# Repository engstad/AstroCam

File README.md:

# AstroCam

My hobby project is to create a camera suitable for astronomy pictures. Here you can follow my work. It is slow going, since I don't have much time to allocate for this. So don't expect too many updates.

For now I have been focusing on three things:

1. understanding Analog Device's H-driver and ADC chip ADDI7013,
2. creating the power circuitry required for the many chips,
3. creating the PCB for the CCD camera chip.

So far, only V0.2 of the ADDI breakout board has been produced and I'm in the process of testing it:

And it works!

So, that means that I'll start working on the camera parts next.

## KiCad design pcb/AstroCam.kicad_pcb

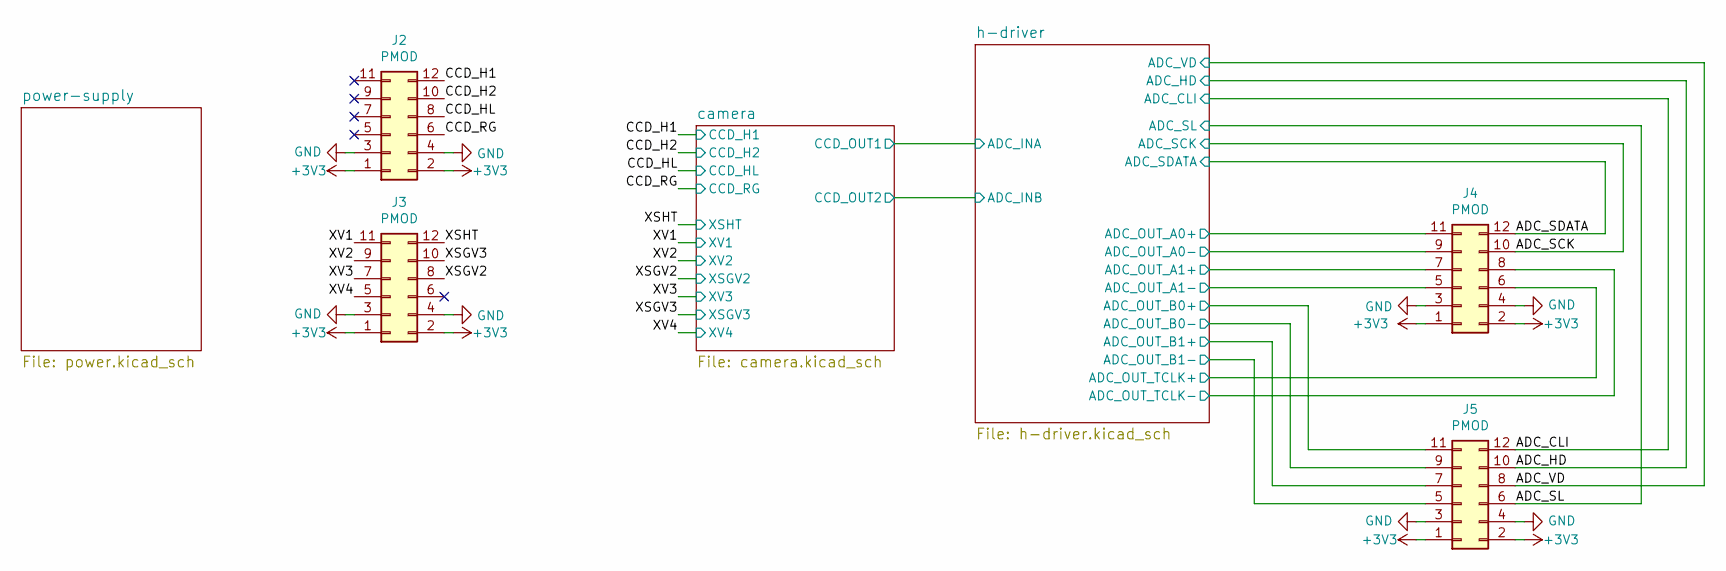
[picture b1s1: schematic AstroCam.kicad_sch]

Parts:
J2, J3, J4, J5: PMOD; PinHeader_2x06_P2.54mm_Horizontal

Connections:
+3V3: J2.1, J2.2, J3.1, J3.2, J4.1, J4.2, J5.1, J5.2; also elsewhere on the board
/ADC_CLI: J5.12; also elsewhere on the board
/ADC_HD: J5.10; also elsewhere on the board
/ADC_SCK: J4.10; also elsewhere on the board
/ADC_SDATA: J4.12; also elsewhere on the board
/ADC_SL: J5.6; also elsewhere on the board
/ADC_VD: J5.8; also elsewhere on the board
/CCD_H1: J2.12; also elsewhere on the board
/CCD_H2: J2.10; also elsewhere on the board
/CCD_HL: J2.8; also elsewhere on the board
/CCD_RG: J2.6; also elsewhere on the board
/XSGV2: J3.8; also elsewhere on the board
/XSGV3: J3.10; also elsewhere on the board
/XSHT: J3.12; also elsewhere on the board
/XV1: J3.11; also elsewhere on the board
/XV2: J3.9; also elsewhere on the board
/XV3: J3.7; also elsewhere on the board
/XV4: J3.5; also elsewhere on the board
/h-driver/ADC_OUT_A0+: J4.11; also elsewhere on the board
/h-driver/ADC_OUT_A0-: J4.9; also elsewhere on the board
/h-driver/ADC_OUT_A1+: J4.7; also elsewhere on the board
/h-driver/ADC_OUT_A1-: J4.5; also elsewhere on the board
/h-driver/ADC_OUT_B0+: J5.11; also elsewhere on the board
/h-driver/ADC_OUT_B0-: J5.9; also elsewhere on the board
/h-driver/ADC_OUT_B1+: J5.7; also elsewhere on the board
/h-driver/ADC_OUT_B1-: J5.5; also elsewhere on the board
/h-driver/ADC_OUT_TCLK+: J4.6; also elsewhere on the board
/h-driver/ADC_OUT_TCLK-: J4.8; also elsewhere on the board

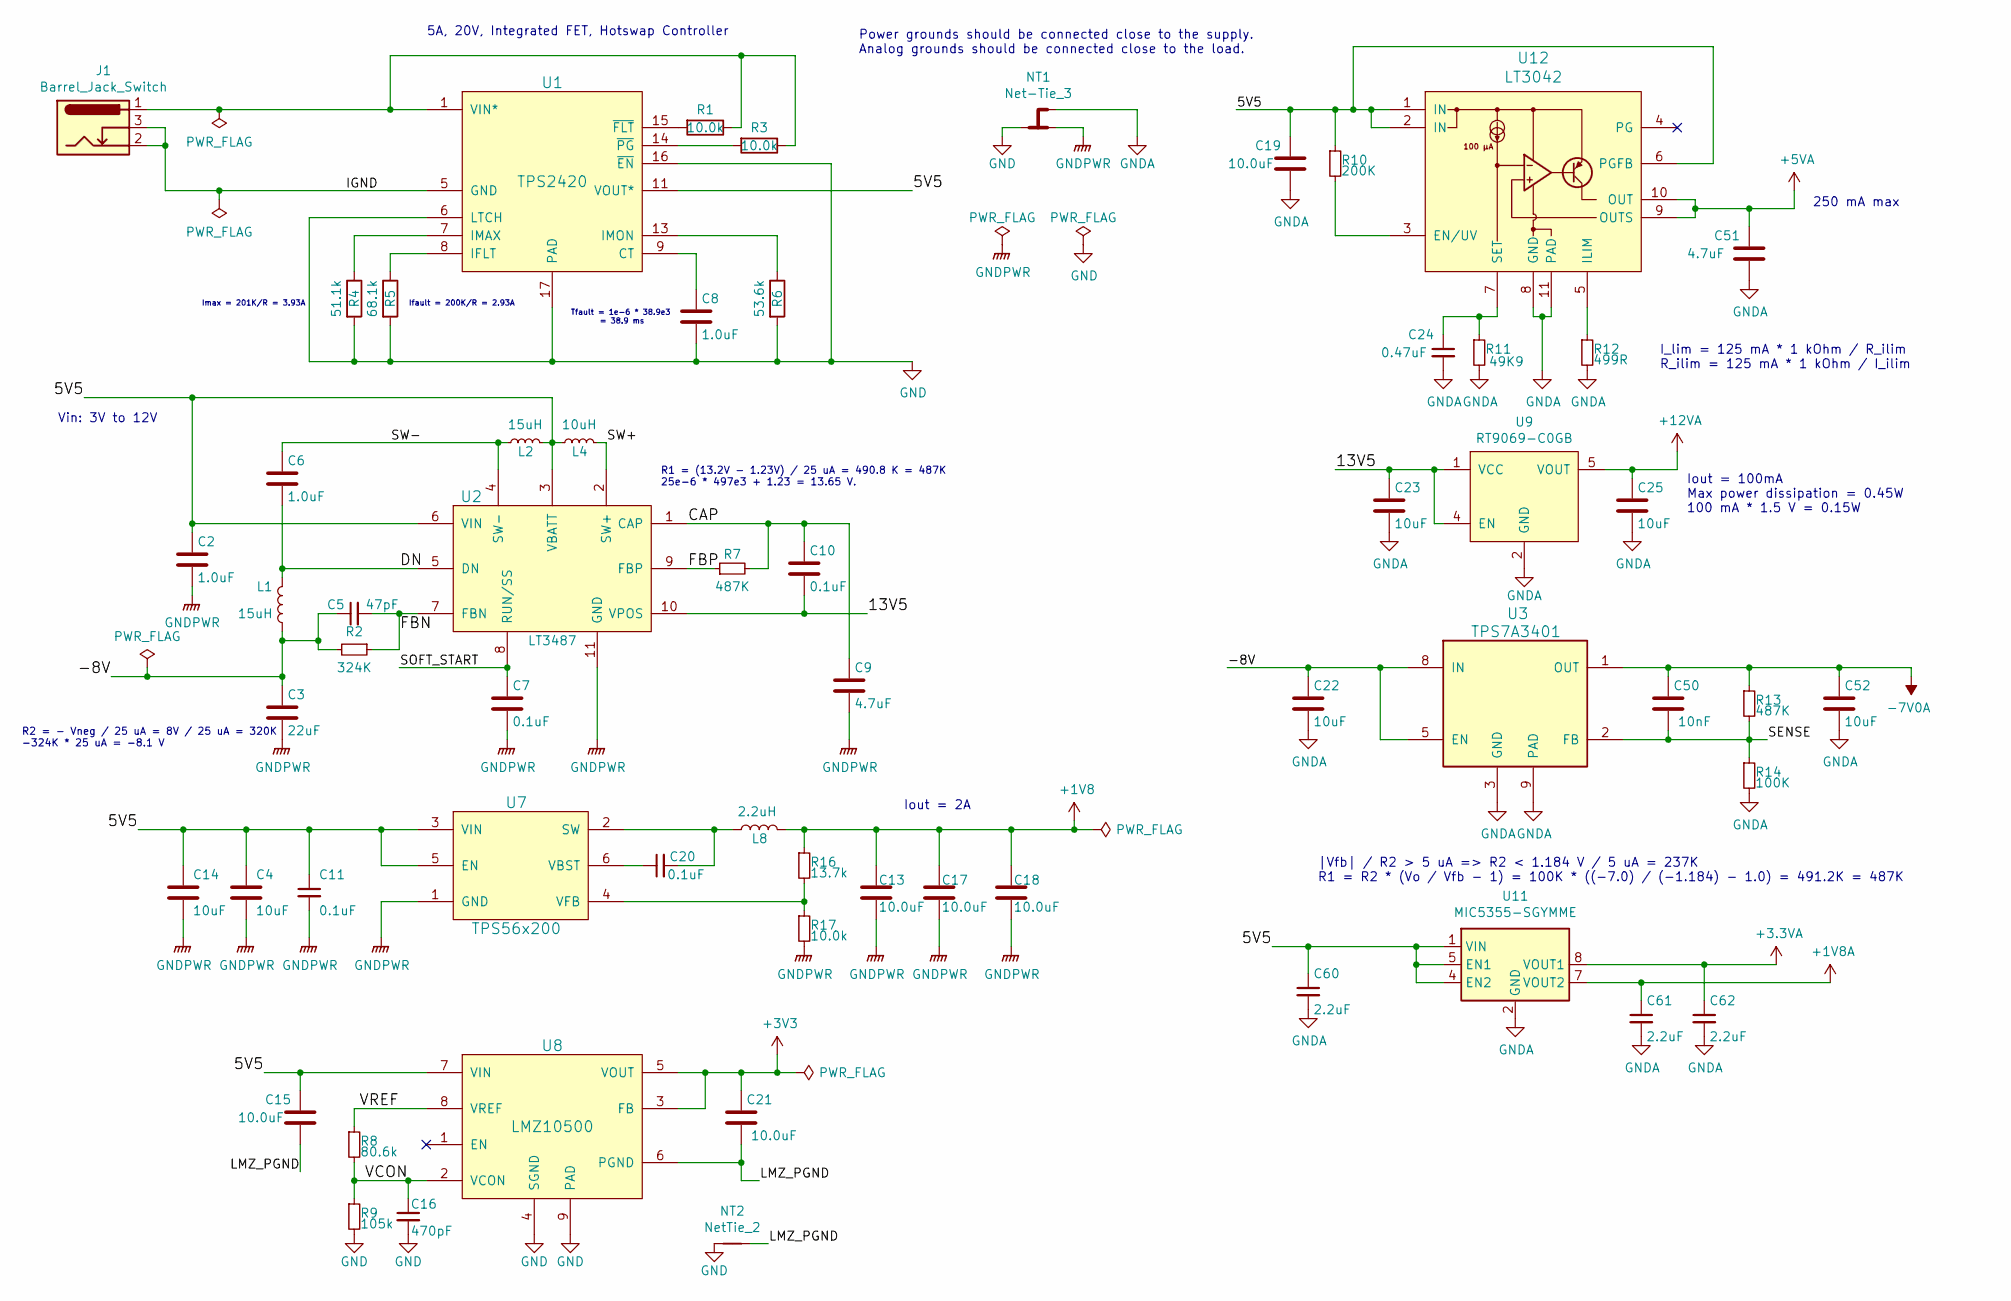
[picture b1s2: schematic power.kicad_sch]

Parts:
C2, C6, C8: 1.0uF; C_0603_1608Metric
C3: 22uF; C_1206_3216Metric
C4, C14: 10uF; C_0805_2012Metric
C5: 47pF; C_0603_1608Metric
C7, C10, C11, C20: 0.1uF; C_0603_1608Metric
C9, C51: 4.7uF; C_0805_2012Metric
C13, C17, C18, C19: 10.0uF; C_1206_3216Metric
C15, C21: 10.0uF; C_0805_2012Metric
C16: 470pF; C_0603_1608Metric
C22, C23, C25, C52: 10uF; C_1206_3216Metric
C24: 0.47uF; C_0603_1608Metric
C50: 10nF; C_0603_1608Metric
C60, C61, C62: 2.2uF; C_0603_1608Metric
J1: Barrel_Jack_Switch; BarrelJack_Wuerth_6941xx301002
L1, L2: 15uH; L_Wurth-4018
L4: 10uH; L_Wurth-4018
L8: 2.2uH; L_0805_2012Metric
NT1: Net-Tie_3; NetTie-3_SMD_Pad0.5mm
NT2: NetTie_2; NetTie-2_THT_Pad0.3mm
R1, R3, R17: 10.0k; R_0603_1608Metric
R2: 324K; R_0603_1608Metric
R4: 51.1k; R_0603_1608Metric
R5: 68.1k; R_0603_1608Metric
R6: 53.6k; R_0603_1608Metric
R7, R13: 487K; R_0603_1608Metric
R8: 80.6k; R_0603_1608Metric
R9: 105k; R_0603_1608Metric
R10: 200K; R_0603_1608Metric
R11: 49K9; R_0603_1608Metric
R12: 499R; R_0603_1608Metric
R14: 100K; R_0603_1608Metric
R16: 13.7k; R_0603_1608Metric
U1: TPS2420; QFN-16-1EP_4x4mm_P0.65mm_EP2.7x2.7mm_ThermalVias
U2: LT3487; DFN-10-1EP_3x3mm_P0.5mm_EP1.7x2.5mm
U3: TPS7A3401; VSSOP-8_3.0x3.0mm_P0.65mm
U7: TPS56x200; SOT-23-6
U8: LMZ10500; Texas_Instruments-LLP-8
U9: RT9069-C0GB; SOT-23-5
U11: MIC5355-SGYMME; MSOP-8-1EP_3x3mm_P0.65mm_EP2.5x3mm_Mask1.73x2.36mm_ThermalV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
U12: LT3042; DFN-10-1EP_3x3mm_P0.5mm_EP1.65x2.38mm_ThermalVias

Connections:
+1V8: C13.1, C17.1, C18.1, L8.2, R16.1; also elsewhere on the board
+1V8A: C61.1, U11.7 (VOUT2)
+3.3VA: C62.1, U11.8 (VOUT1); also elsewhere on the board
+3V3: C21.1, U8.3 (FB), U8.5 (VOUT); also elsewhere on the board
+5VA: C51.1, U12.9 (OUTS), U12.10 (OUT); also elsewhere on the board
+12VA: C25.1, U9.5 (VOUT); also elsewhere on the board
-7V0A: C50.1, C52.1, R13.1, U3.1 (OUT); also elsewhere on the board
/power-supply/5V5: C2.1, C4.1, C11.1, C14.1, C15.1, C19.1, C60.1, L2.2, L4.1, R10.1, U1.10 (VOUT*), U1.11 (VOUT*), U1.12 (VOUT*), U2.3 (VBATT), U2.6 (VIN), U7.3 (VIN), U7.5 (EN), U8.7 (VIN), U11.1 (VIN), U11.4 (EN2), U11.5 (EN1), U12.1 (IN), U12.2 (IN), U12.6 (PGFB)
/power-supply/13V5: C10.2, C23.1, U2.10 (VPOS), U9.1 (VCC), U9.4 (EN)
/power-supply/-8V: C3.1, C5.1, C22.1, L1.1, R2.2, U3.5 (EN), U3.8 (IN)
/power-supply/CAP: C9.1, C10.1, R7.2, U2.1 (CAP)
/power-supply/DN: C6.2, L1.2, U2.5 (DN)
/power-supply/FBN: C5.2, R2.1, U2.7 (FBN)
/power-supply/FBP: R7.1, U2.9 (FBP)
/power-supply/IGND: J1.2, J1.3, U1.5 (GND)
/power-supply/LMZ_PGND: C15.2, C21.2, NT2.2, U8.6 (PGND)
/power-supply/SENSE: C50.2, R13.2, R14.1, U3.2 (FB)
/power-supply/SOFT_START: C7.1, U2.8 (RUN/SS)
/power-supply/SW+: L4.2, U2.2 (SW+)
/power-supply/SW-: C6.1, L2.1, U2.4 (SW-)
/power-supply/VCON: C16.1, R8.2, R9.1, U8.2 (VCON)
/power-supply/VREF: R8.1, U8.8 (VREF)
GNDPWR: C2.2, C3.2, C4.2, C7.2, C9.2, C11.2, C13.2, C14.2, C17.2, C18.2, NT1.1, R17.2, U2.11 (GND), U7.1 (GND)
unnamed: C8.1, U1.9 (CT)
unnamed: R5.1, U1.8 (IFLT)
unnamed: R4.1, U1.7 (IMAX)
unnamed: R6.1, U1.13 (IMON)
unnamed: R1.2, U1.15 (~FLT)
unnamed: R3.2, U1.14 (~PG)
unnamed: C20.2, L8.1, U7.2 (SW)
unnamed: C20.1, U7.6 (VBST)
unnamed: R16.2, R17.1, U7.4 (VFB)
unnamed: R10.2, U12.3 (EN/UV)
unnamed: R12.1, U12.5 (ILIM)
unnamed: C24.1, R11.1, U12.7 (SET)
VIN*: J1.1, R1.1, R3.1, U1.1 (VIN*), U1.2 (VIN*), U1.3 (VIN*), U1.4 (VIN*)

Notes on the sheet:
R2 = - Vneg / 25 uA = 8V / 25 uA = 320K -324K * 25 uA = -8.1 V
Iout = 2A
I_lim = 125 mA * 1 kOhm / R_ilim R_ilim = 125 mA * 1 kOhm / I_ilim
Tfault = 1e-6 * 38.9e3 = 38.9 ms
250 mA max
Vin: 3V to 12V
Ifault = 200K/R = 2.93A
Imax = 201K/R = 3.93A
Power grounds should be connected close to the supply. Analog grounds should be connected close to the load.
R1 = (13.2V - 1.23V) / 25 uA = 490.8 K = 487K 25e-6 * 497e3 + 1.23 = 13.65 V.
|Vfb| / R2 > 5 uA => R2 < 1.184 V / 5 uA = 237K R1 = R2 * (Vo / Vfb - 1) = 100K * ((-7.0) / (-1.184) - 1.0) = 491.2K = 487K
Iout = 100mA Max power dissipation = 0.45W 100 mA * 1.5 V = 0.15W
5A, 20V, Integrated FET, Hotswap Controller

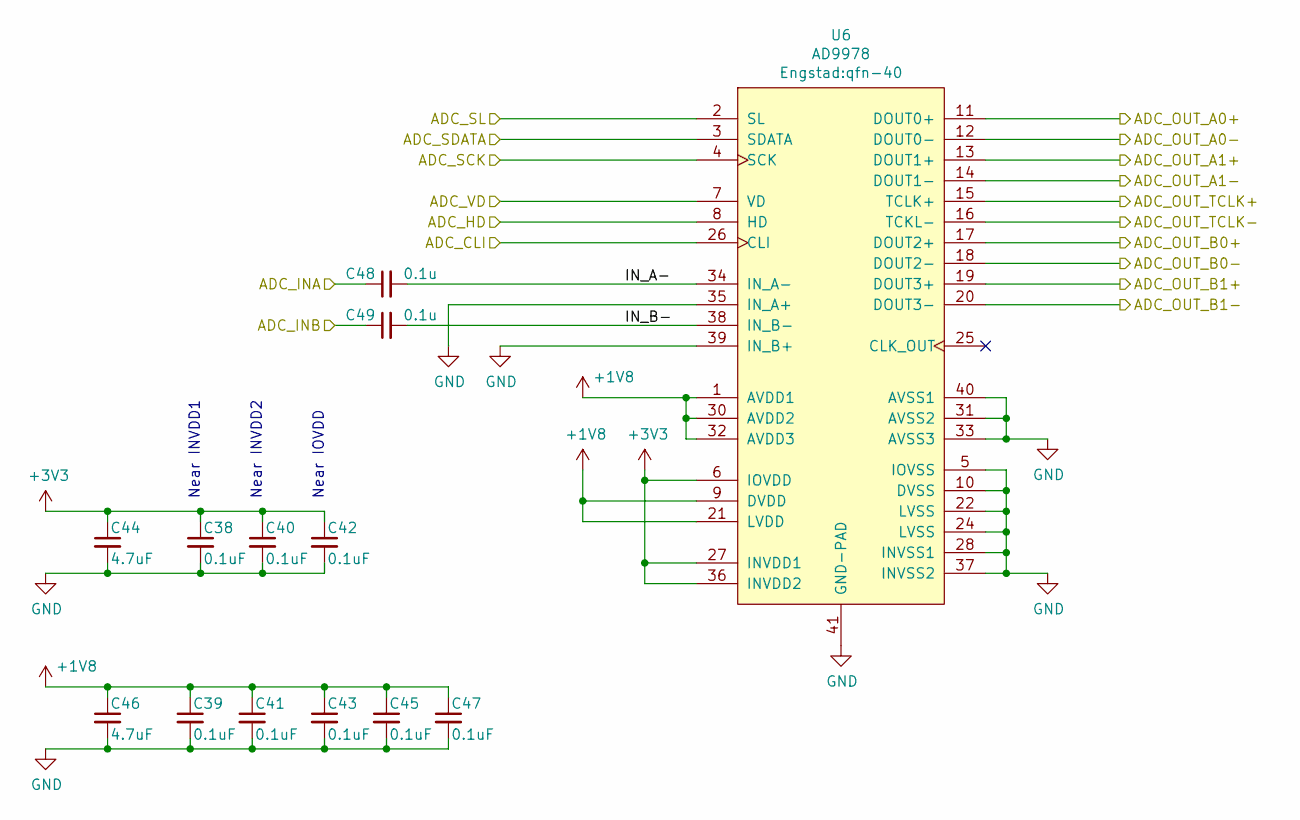
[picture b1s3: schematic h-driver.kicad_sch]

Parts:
C38, C39, C40, C41, C42, C43, C45, C47: 0.1uF; C_0603_1608Metric
C44, C46: 4.7uF; C_0805_2012Metric
C48, C49: 0.1u; C_0603_1608Metric
U6: AD9978; qfn-40

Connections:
+1V8: C39.1, C41.1, C43.1, C45.1, C46.1, C47.1, U6.1 (AVDD1), U6.9 (DVDD), U6.21 (LVDD), U6.30 (AVDD2), U6.32 (AVDD3); also elsewhere on the board
+3V3: C38.1, C40.1, C42.1, C44.1, U6.6 (IOVDD), U6.27 (INVDD1), U6.36 (INVDD2); also elsewhere on the board
/ADC_CLI: U6.26 (CLI); also elsewhere on the board
/ADC_HD: U6.8 (HD); also elsewhere on the board
/ADC_SCK: U6.4 (SCK); also elsewhere on the board
/ADC_SDATA: U6.3 (SDATA); also elsewhere on the board
/ADC_SL: U6.2 (SL); also elsewhere on the board
/ADC_VD: U6.7 (VD); also elsewhere on the board
/camera/CCD_OUT1: C48.1; also elsewhere on the board
/camera/CCD_OUT2: C49.1; also elsewhere on the board
/h-driver/ADC_OUT_A0+: U6.11 (DOUT0+); also elsewhere on the board
/h-driver/ADC_OUT_A0-: U6.12 (DOUT0-); also elsewhere on the board
/h-driver/ADC_OUT_A1+: U6.13 (DOUT1+); also elsewhere on the board
/h-driver/ADC_OUT_A1-: U6.14 (DOUT1-); also elsewhere on the board
/h-driver/ADC_OUT_B0+: U6.17 (DOUT2+); also elsewhere on the board
/h-driver/ADC_OUT_B0-: U6.18 (DOUT2-); also elsewhere on the board
/h-driver/ADC_OUT_B1+: U6.19 (DOUT3+); also elsewhere on the board
/h-driver/ADC_OUT_B1-: U6.20 (DOUT3-); also elsewhere on the board
/h-driver/ADC_OUT_TCLK+: U6.15 (TCLK+); also elsewhere on the board
/h-driver/ADC_OUT_TCLK-: U6.16 (TCKL-); also elsewhere on the board
/h-driver/IN_A-: C48.2, U6.34 (IN_A-)
/h-driver/IN_B-: C49.2, U6.38 (IN_B-)

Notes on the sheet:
Near IOVDD
Near INVDD1
Near INVDD2

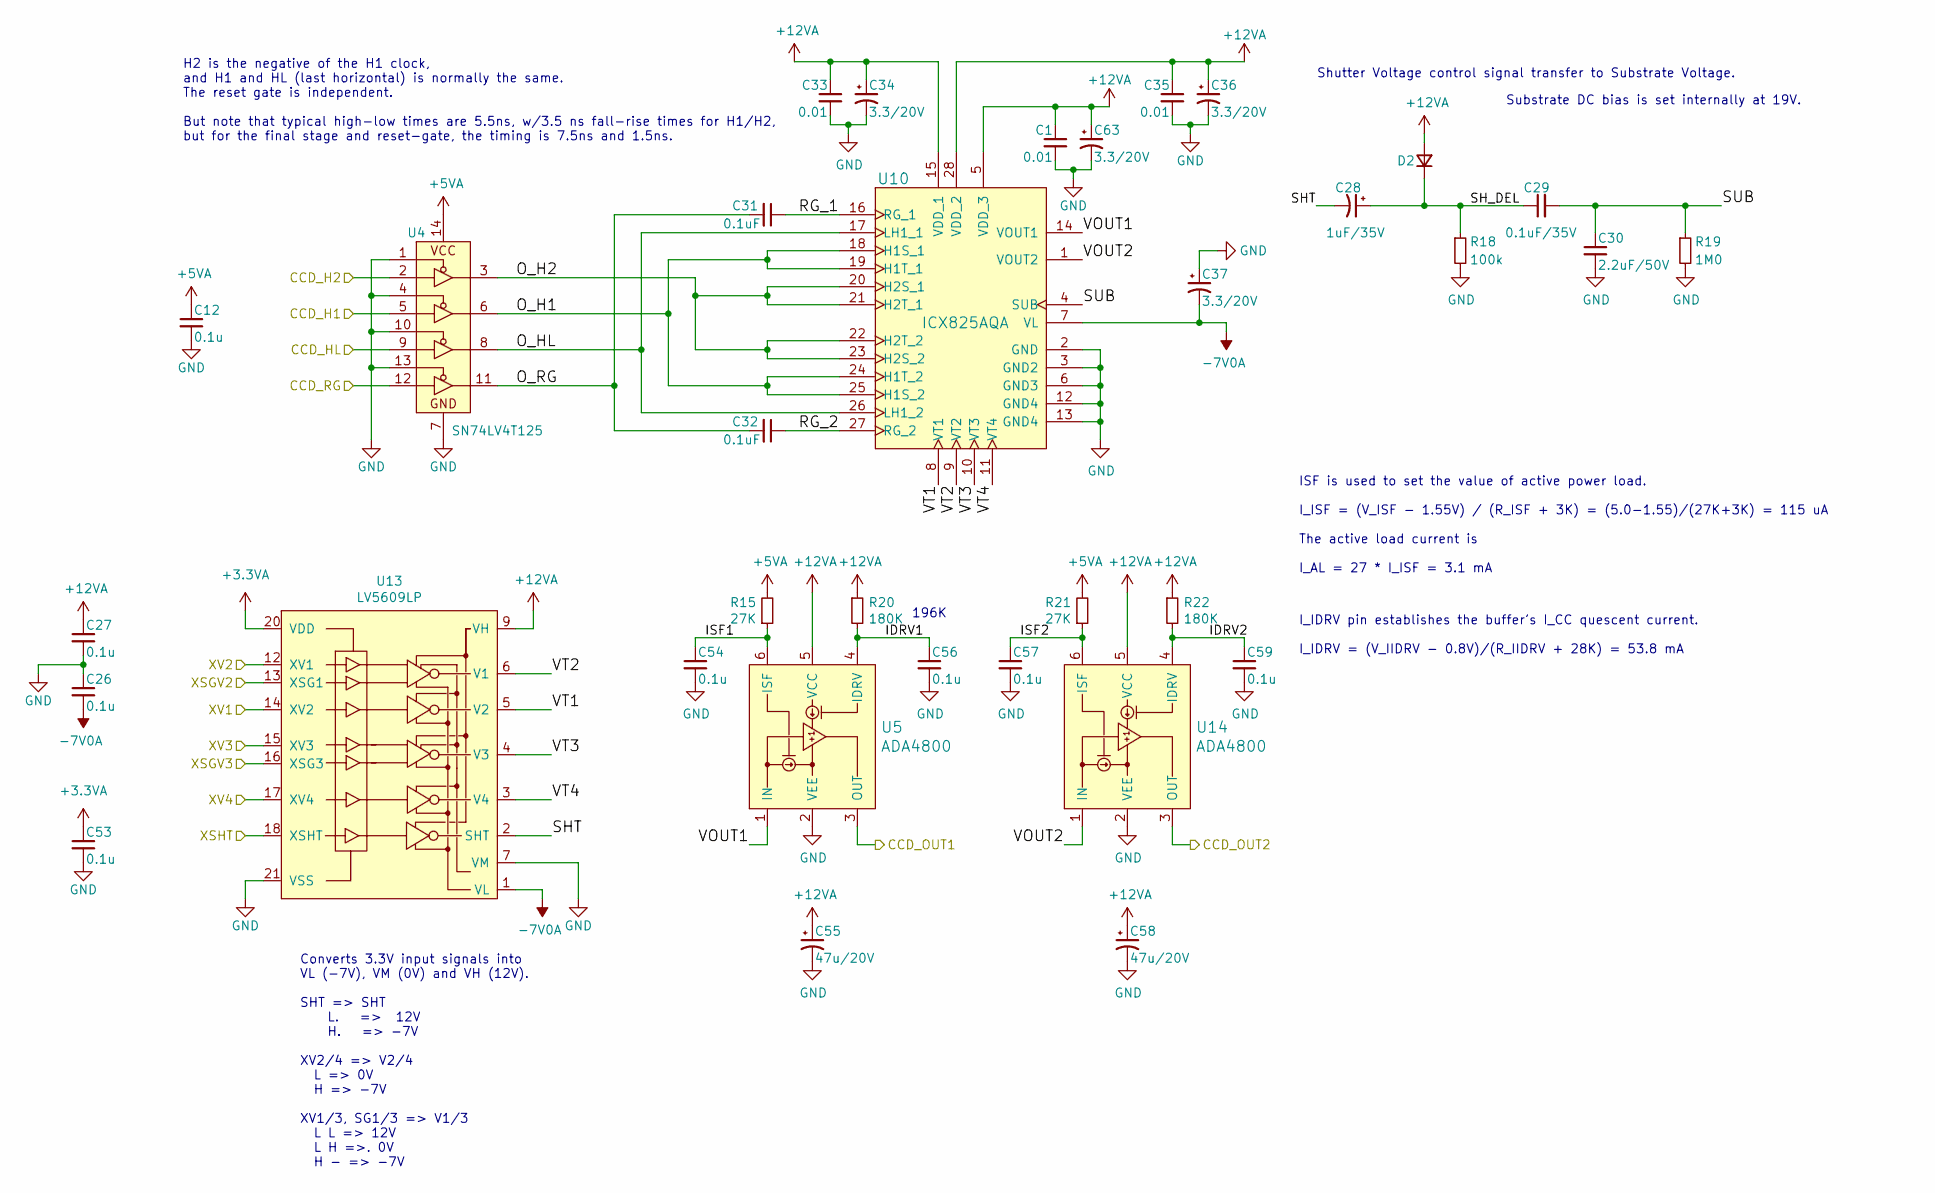
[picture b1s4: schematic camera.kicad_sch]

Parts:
C1, C33, C35: 0.01; C_0603_1608Metric
C12, C26, C27, C53, C54, C56, C57, C59: 0.1u; C_0603_1608Metric
C28: 1uF/35V; CP_EIA-1608-08_AVX-J
C29: 0.1uF/35V; C_0805_2012Metric
C30: 2.2uF/50V; C_0805_2012Metric
C31, C32: 0.1uF; C_0603_1608Metric
C34: 3.3/20V; CP_EIA-3528-12_Kemet-T
C36, C37, C63: 3.3/20V; CP_EIA-1608-08_AVX-J
C55, C58: 47u/20V; C_1206_3216Metric
D2: D; D_SOD-123
R15, R21: 27K; R_0603_1608Metric
R18: 100k; R_0603_1608Metric
R19: 1M0; R_0603_1608Metric
R20, R22: 180K; R_0603_1608Metric
U4: SN74LV4T125; Texas_R-PDSO-G14
U5, U14: ADA4800; lfcsp-cp-6-4
U10: ICX825AQA; ICX825
U13: LV5609LP; ON_Semiconductor-VCT24-3.5x3.5mm

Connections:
+3.3VA: C53.1, U13.20 (VDD); also elsewhere on the board
+5VA: C12.1, R15.2, R21.2, U4.14 (VCC); also elsewhere on the board
+12VA: C1.1, C27.1, C33.1, C34.1, C35.1, C36.1, C55.1, C58.1, C63.1, D2.2 (A), R20.1, R22.1, U5.5 (VCC), U10.5 (VDD_3), U10.15 (VDD_1), U10.28 (VDD_2), U13.9 (VH), U14.5 (VCC); also elsewhere on the board
-7V0A: C26.2, C37.2, U10.7 (VL), U13.1 (VL); also elsewhere on the board
/CCD_H1: U4.5 (2A); also elsewhere on the board
/CCD_H2: U4.2 (1A); also elsewhere on the board
/CCD_HL: U4.9 (3A); also elsewhere on the board
/CCD_RG: U4.12 (4A); also elsewhere on the board
/XSGV2: U13.13 (XSG1); also elsewhere on the board
/XSGV3: U13.16 (XSG3); also elsewhere on the board
/XSHT: U13.18 (XSHT); also elsewhere on the board
/XV1: U13.14 (XV2); also elsewhere on the board
/XV2: U13.12 (XV1); also elsewhere on the board
/XV3: U13.15 (XV3); also elsewhere on the board
/XV4: U13.17 (XV4); also elsewhere on the board
/camera/CCD_OUT1: U5.3 (OUT); also elsewhere on the board
/camera/CCD_OUT2: U14.3 (OUT); also elsewhere on the board
/camera/IDRV1: C56.1, R20.2, U5.4 (IDRV)
/camera/IDRV2: C59.1, R22.2, U14.4 (IDRV)
/camera/ISF1: C54.1, R15.1, U5.6 (ISF)
/camera/ISF2: C57.1, R21.1, U14.6 (ISF)
/camera/O_H1: U4.6 (2Y), U10.18 (H1S_1), U10.19 (H1T_1), U10.24 (H1T_2), U10.25 (H1S_2)
/camera/O_H2: U4.3 (1Y), U10.20 (H2S_1), U10.21 (H2T_1), U10.22 (H2T_2), U10.23 (H2S_2)
/camera/O_HL: U4.8 (3Y), U10.17 (LH1_1), U10.26 (LH1_2)
/camera/O_RG: C31.2, C32.2, U4.11 (4Y)
/camera/RG_1: C31.1, U10.16 (RG_1)
/camera/RG_2: C32.1, U10.27 (RG_2)
/camera/SHT: C28.2, U13.2 (SHT)
/camera/SH_DEL: C28.1, C29.1, D2.1 (K), R18.1
/camera/SUB: C29.2, C30.1, R19.1, U10.4 (SUB)
/camera/VOUT1: U5.1 (IN), U10.14 (VOUT1)
/camera/VOUT2: U10.1 (VOUT2), U14.1 (IN)
/camera/VT1: U10.8 (VT1), U13.5 (V2)
/camera/VT2: U10.9 (VT2), U13.6 (V1)
/camera/VT3: U10.10 (VT3), U13.4 (V3)
/camera/VT4: U10.11 (VT4), U13.3 (V4)

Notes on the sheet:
196K
Shutter Voltage control signal transfer to Substrate Voltage.
Substrate DC bias is set internally at 19V.
ISF is used to set the value of active power load. I_ISF = (V_ISF - 1.55V) / (R_ISF + 3K) = (5.0-1.55)/(27K+3K) = 115 uA The active load current is I_AL = 27 * I_ISF = 3.1 mA
H2 is the negative of the H1 clock, and H1 and HL (last horizontal) is normally the same. The reset gate is independent. But note that typical high-low times are 5.5ns, w/3.5 ns fall-rise times for H1/H2, but for the final stage and reset-gate, the timing is 7.5ns and 1.5ns.
I_IDRV pin establishes the buffer's I_CC quescent current. I_IDRV = (V_IIDRV - 0.8V)/(R_IIDRV + 28K) = 53.8 mA
Converts 3.3V input signals into VL (-7V), VM (0V) and VH (12V). SHT => SHT L. => 12V H. => -7V XV2/4 => V2/4 L => 0V H => -7V XV1/3, SG1/3 => V1/3 L L => 12V L H =>. 0V H - => -7V

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
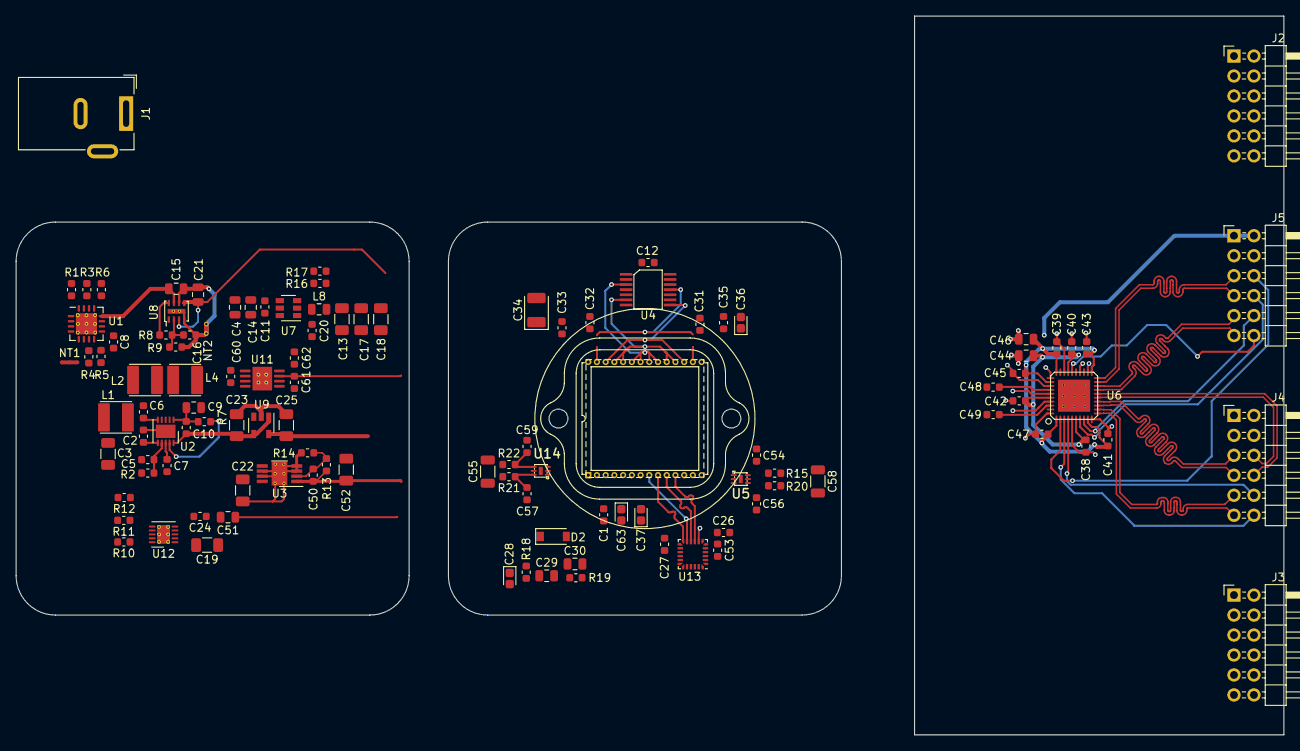
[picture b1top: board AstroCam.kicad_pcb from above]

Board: 2 copper layers, 161.3 x 91.4 mm, 111 parts (0 on the bottom side), 87 nets.

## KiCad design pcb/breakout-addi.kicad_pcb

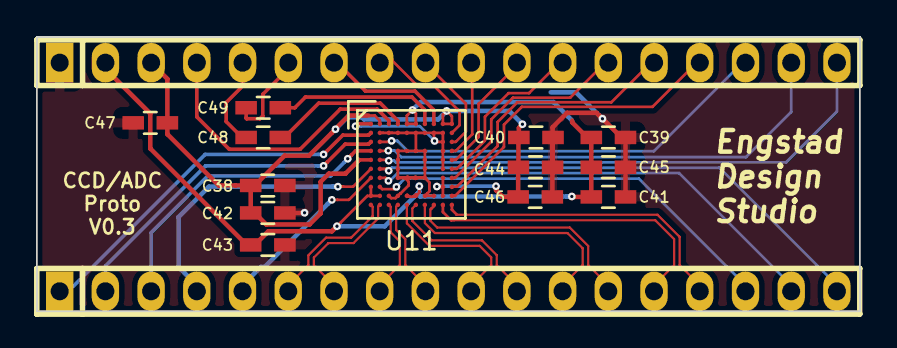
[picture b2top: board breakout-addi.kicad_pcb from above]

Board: 2 copper layers, 45.7 x 15.2 mm, 15 parts (0 on the bottom side), 38 nets.

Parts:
C38, C39, C40, C41, C42, C43, C44, C45, C46: 0.1uF; C_0603_HandSoldering
C47: 4.7uF; C_0603_HandSoldering
C48, C49: 0.1u; C_0603_HandSoldering
P2, P3: CONN_01X18; pin_strip_18
U11: ADDI7013; csp-bga-bc-76-3

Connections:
/h-driver/1V8: C39.1, C41.1, C43.1, C45.1, P3.2, U11.A5, U11.A6, U11.H1, U11.J1, U11.J2, U11.J5, U11.J6
/h-driver/3V3: C38.1, C40.1, C42.1, C44.1, C46.1, C47.1, P3.3, U11.A2, U11.A9, U11.A10, U11.E1, U11.G9, U11.H9, U11.J9
/h-driver/A0+: P2.6, U11.K1
/h-driver/A0-: P2.7, U11.K2
/h-driver/A1+: P2.8, U11.K3
/h-driver/A1-: P2.9, U11.K4
/h-driver/B0+: P2.12, U11.K7
/h-driver/B0-: P2.13, U11.K8
/h-driver/B1+: P2.14, U11.K9
/h-driver/B1-: P2.15, U11.K10
/h-driver/CLI: P2.1, U11.B1
/h-driver/GP01: P2.2, U11.C1
/h-driver/GP02: P2.3, U11.D1
/h-driver/GP03: P2.4, U11.F1
/h-driver/GP04: P2.5, U11.G1
/h-driver/H1: P3.13, U11.G10
/h-driver/H2: P3.12, U11.F10
/h-driver/H3: P3.11, U11.E10
/h-driver/H4: P3.10, U11.D10
/h-driver/HD: P2.17, U11.G2
/h-driver/HL1: P3.14, U11.H10
/h-driver/HL2: P3.9, U11.C10
/h-driver/IN_A+: C48.1, P3.5
/h-driver/IN_A-: P3.4, U11.A3
/h-driver/IN_B+: C49.1, P3.6
/h-driver/IN_B-: P3.7, U11.A8
/h-driver/RG1: P3.15, U11.J10
/h-driver/RG2: P3.8, U11.B10
/h-driver/SCK: P3.17, U11.D2
/h-driver/SDATA: P3.18, U11.E2
/h-driver/SL: P3.16, U11.C2
/h-driver/SYNC: P2.18, U11.F2
/h-driver/TCLK+: P2.10, U11.K5
/h-driver/TCLK-: P2.11, U11.K6
/h-driver/VD: P2.16, U11.H2
GND: C38.2, C39.2, C40.2, C41.2, C42.2, C43.2, C44.2, C45.2, C46.2, C47.2, P3.1, U11.A1, U11.B2, U11.B3, U11.B4, U11.B5, U11.B6, U11.B7, U11.B8, U11.B9, U11.C9, U11.D4, U11.D5, U11.D6, U11.D7, U11.D9, U11.E4, U11.E7, U11.E9, U11.F4, U11.F7, U11.F9, U11.G4, U11.G5, U11.G6, U11.G7, U11.J3, U11.J4, U11.J7, U11.J8
unnamed: C48.2, U11.A4
unnamed: C49.2, U11.A7

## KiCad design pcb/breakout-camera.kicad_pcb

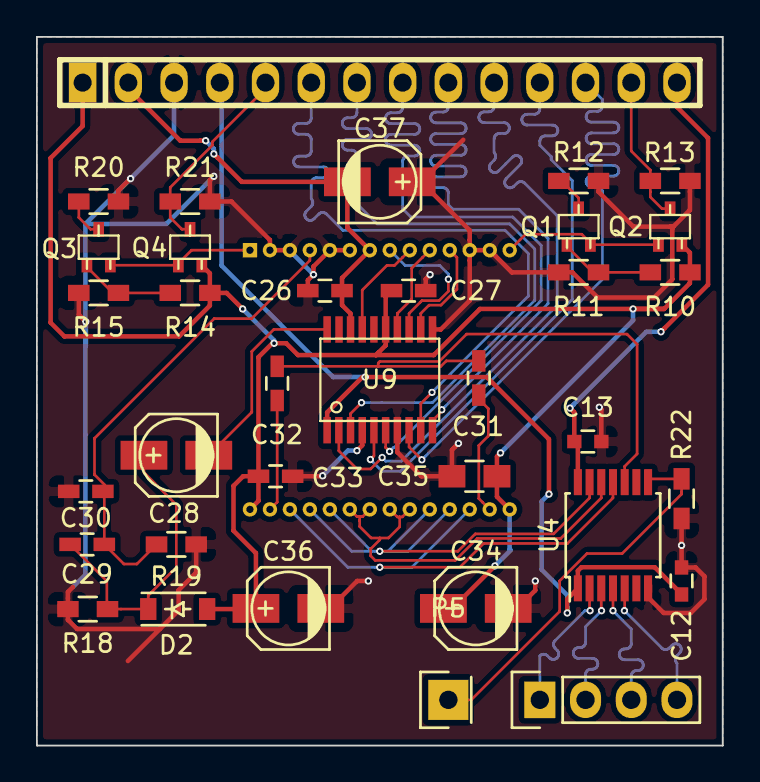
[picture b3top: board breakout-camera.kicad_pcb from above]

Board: 2 copper layers, 38.1 x 39.4 mm, 36 parts (1 on the bottom side), 38 nets.

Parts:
C12, C13: 0.1u; C_0603
C26, C27: 0.1u; C_0603_HandSoldering
C28: 1u/35V; c_elec_4x5.3
C29: 0.1uF; C_0603_HandSoldering
C30: 2200pF; C_0603_HandSoldering
C31, C32: 0.1; C_0603_HandSoldering
C33: 0.01; C_0603_HandSoldering
C34, C36, C37: 3.3/20V; c_elec_4x5.3
C35: 0.01; C_0805_HandSoldering
D2: D; SOD-123
P4: CONN_01X04; Socket_Strip_Straight_1x04
P5: CONN_01X01; Socket_Strip_Straight_1x01
P10: CONN_01X14; pin_strip_14
Q1, Q3: 2SC5095; sot323
Q2, Q4: MT3S20TU; sot323
R10, R11, R14, R15: 10K; R_0603_HandSoldering
R12, R20: 1.17K; R_0603_HandSoldering
R13, R21: 1.74K; R_0603_HandSoldering
R18: 100k; R_0603_HandSoldering
R19: 1M0; R_0603_HandSoldering
R22: 10.0k; R_0603_HandSoldering
U4: TXB0104; TSSOP-14_4.4x5mm_Pitch0.65mm
U9: CXD3400N; tssop-20
U10: ICX825AQA; ICX825

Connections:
/camera/3V3: C12.1, P10.4, U4.1, U9.1
/camera/5V0: C13.1, P10.14, U4.14
/camera/12V: C27.1, C33.2, C34.1, C35.2, C36.1, D2.2, P10.1, Q2.3, Q4.3, R10.1, R14.1, U9.15, U10.15, U10.28
/camera/-7V: C26.1, C37.2, P10.2, U9.18, U10.7
/camera/B1: Q1.1, R10.2, R11.1
/camera/B2: Q3.1, R14.2, R15.1
/camera/CCD_OUT1: P10.13, Q2.2, R13.1
/camera/CCD_OUT2: P10.5, Q4.2, R21.1
/camera/E1: Q1.2, R12.1
/camera/E2: Q3.2, R20.1
/camera/ENH: P5.1, R22.1, U4.8
/camera/H1: P4.1, U4.2
/camera/H1S_1: U4.13, U10.18, U10.19, U10.24, U10.25
/camera/H2: P4.2, U4.3
/camera/H2S_1: U4.12, U10.20, U10.21, U10.22, U10.23
/camera/HL: P4.3, U4.4
/camera/LH1_1: U4.11, U10.17, U10.26
/camera/ORG: C31.2, C32.2, U4.10
/camera/RG: P4.4, U4.5
/camera/RG_1: C31.1, U10.16
/camera/RG_2: C32.1, U10.27
/camera/SUB: C29.2, C30.1, R19.1, U10.4
/camera/VOUT1: Q1.3, Q2.1, U10.14
/camera/VOUT2: Q3.3, Q4.1, U10.1
/camera/VT1: U9.13, U10.8
/camera/VT2: U9.17, U10.9
/camera/VT3: U9.14, U10.10
/camera/VT4: U9.12, U10.11
/camera/XSGV2: P10.11, U9.5
/camera/XSGV3: P10.12, U9.8
/camera/XSHT: P10.10, U9.2
/camera/XV1: P10.6, U9.9
/camera/XV2: P10.7, U9.3
/camera/XV3: P10.8, U9.6
/camera/XV4: P10.9, U9.10
GND: C12.2, C13.2, C26.2, C27.2, C30.2, C33.1, C34.2, C35.1, C36.2, C37.1, P10.3, R11.2, R12.2, R13.2, R15.2, R18.2, R19.2, R20.2, R21.2, R22.2, U4.7, U9.4, U9.7, U9.11, U10.2, U10.3, U10.5, U10.6, U10.12, U10.13
unnamed: C28.1, C29.1, D2.1, R18.1
unnamed: C28.2, U9.20

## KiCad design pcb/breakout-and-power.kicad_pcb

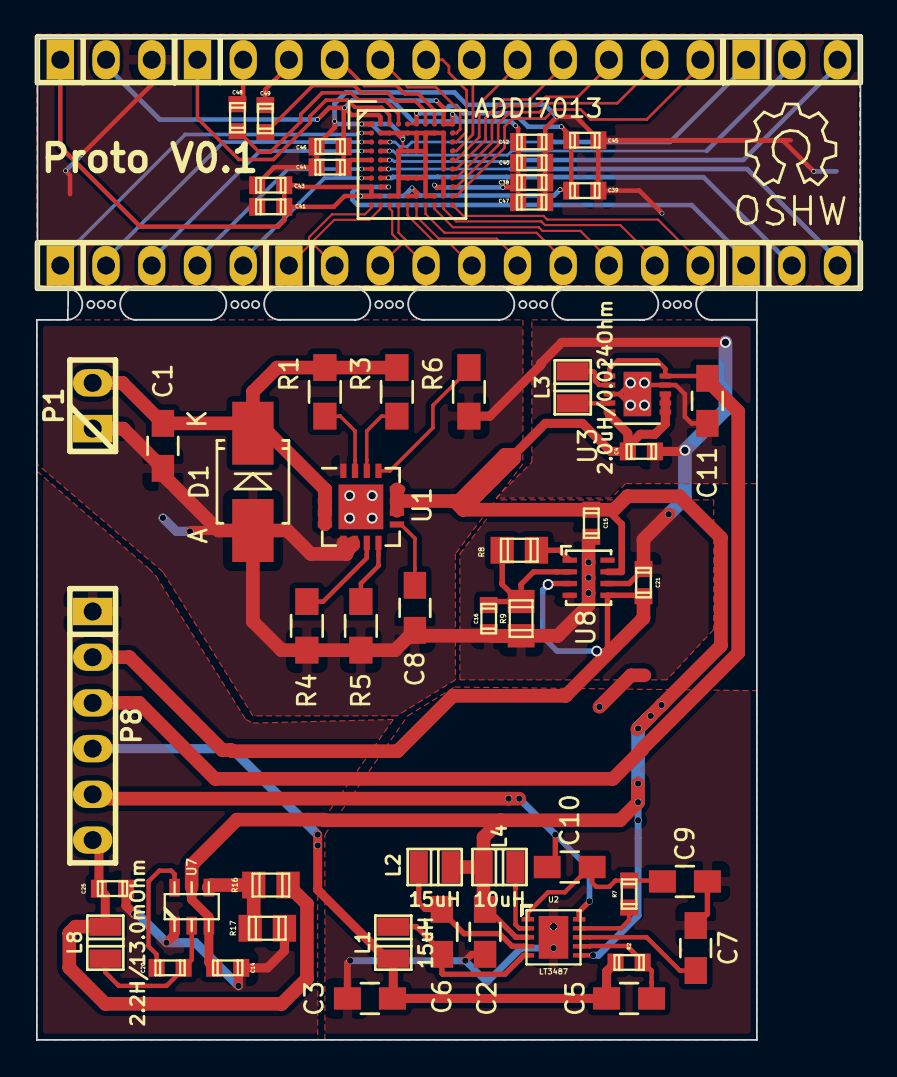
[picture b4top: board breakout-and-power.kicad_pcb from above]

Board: 2 copper layers, 45.8 x 55.7 mm, 60 parts (0 on the bottom side), 66 nets.

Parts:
C1, C2, C6: 1.0uF; C_0805_HandSoldering
C3, C5: 47pF; C_0805_HandSoldering
C4: 2.20uF/2.80Mohm; c_0603
C7: 100nF; C_0805_HandSoldering
C8: 1.0F/11mOhm; C_0805_HandSoldering
C9: 4.7uF; C_0805_HandSoldering
C10: 0.1uF; C_0805_HandSoldering
C11: 10uF; C_0805_HandSoldering
C14: 10.0F/3.0mOhm; c_0603
C15: 10.0F/9Mohm; c_0603
C16: 470pF; c_0603
C20: 100nF; c_0603
C21: 10.0uF/9.0Mohm; c_0603
C25: 47F/3Mohm; c_0603
C38, C39, C40, C41, C42, C43, C44, C45, C46: 0.1uF; c_0603
C47: 4.7uF; c_0603
C48, C49: 0.1u; c_0603
D1: 9V/5W; Diode-SMB_Handsoldering
L1, L2: 15uH; inductor_smd_0805
L3: 2.0uH/0.024Ohm; inductor_smd_0805
L4: 10uH; inductor_smd_0805
L8: 2.2H/13.0mOhm; inductor_smd_0805
P1: CONN_01X02; pin_strip_2
P2: CONN_01X05; pin_strip_5
P3: CONN_01X10; pin_strip_10
P4, P6, P7: CONN_01X03; pin_strip_3
P5: CONN_01X12; pin_strip_12
P8: CONN_01X06; pin_socket_6
R1, R3: 10.0k; R_0805_HandSoldering
R2, R7: 324k; r_0603
R4: 51.1k; R_0805_HandSoldering
R5: 68.1k; R_0805_HandSoldering
R6: 53.6k; R_0805_HandSoldering
R8: 80.6k; r_0805
R9: 105k; r_0805
R16: 13.7k; r_0805
R17: 10.0k; r_0805
U1: TPS2420; QFN-16-1EP_4x4mm_Pitch0.65mm
U2: LT3487; dfn10-3x3
U3: TPS63002; DFN-10-1EP_3x3mm_Pitch0.5mm
U7: TPS56x200; sot23-6
U8: LMZ10500; llp-8
U11: ADDI7013; csp-bga-bc-76-3

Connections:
/h-driver/1V8: C39.1, C41.1, C43.1, C45.1, P7.1, U11.A5, U11.A6, U11.H1, U11.J1, U11.J2, U11.J5, U11.J6
/h-driver/3V3: C38.1, C40.1, C42.1, C44.1, C46.1, C47.1, P7.2, U11.A2, U11.A9, U11.A10, U11.E1, U11.G9, U11.H9, U11.J9
/h-driver/A0+: P3.1, U11.K1
/h-driver/A0-: P3.2, U11.K2
/h-driver/A1+: P3.3, U11.K3
/h-driver/A1-: P3.4, U11.K4
/h-driver/B0+: P3.7, U11.K7
/h-driver/B0-: P3.8, U11.K8
/h-driver/B1+: P3.9, U11.K9
/h-driver/B1-: P3.10, U11.K10
/h-driver/CLI: P2.1, U11.B1
/h-driver/GND: C38.2, C39.2, C40.2, C41.2, C42.2, C43.2, C44.2, C45.2, C46.2, C47.2, P7.3, U11.A1, U11.B2, U11.B3, U11.B4, U11.B5, U11.B6, U11.B7, U11.B8, U11.B9, U11.C9, U11.D4, U11.D5, U11.D6, U11.D7, U11.D9, U11.E4, U11.E7, U11.E9, U11.F4, U11.F7, U11.F9, U11.G4, U11.G5, U11.G6, U11.G7, U11.J3, U11.J4, U11.J7, U11.J8
/h-driver/GP01: P2.2, U11.C1
/h-driver/GP02: P2.3, U11.D1
/h-driver/GP03: P2.4, U11.F1
/h-driver/GP04: P2.5, U11.G1
/h-driver/H1: P5.10, U11.G10
/h-driver/H2: P5.9, U11.F10
/h-driver/H3: P5.8, U11.E10
/h-driver/H4: P5.7, U11.D10
/h-driver/HD: P6.2, U11.G2
/h-driver/HL1: P5.11, U11.H10
/h-driver/HL2: P5.6, U11.C10
/h-driver/IN_A+: C48.1, P5.2
/h-driver/IN_A-: P5.1, U11.A3
/h-driver/IN_B+: C49.1, P5.3
/h-driver/IN_B-: P5.4, U11.A8
/h-driver/RG1: P5.12, U11.J10
/h-driver/RG2: P5.5, U11.B10
/h-driver/SCK: P4.2, U11.D2
/h-driver/SDATA: P4.3, U11.E2
/h-driver/SL: P4.1, U11.C2
/h-driver/SYNC: P6.3, U11.F2
/h-driver/TCLK+: P3.5, U11.K5
/h-driver/TCLK-: P3.6, U11.K6
/h-driver/VD: P6.1, U11.H2
/power-supply/1V8: C25.1, L8.2, P8.6, R16.1
/power-supply/3V3: C21.1, P8.2, U8.3, U8.5
/power-supply/5V0: C11.1, P8.3, U3.1, U3.10
/power-supply/5V5: C2.1, C4.1, C14.1, C15.1, L2.2, L4.1, U1.10, U1.11, U1.12, U2.3, U2.6, U3.5, U3.6, U3.7, U3.8, U7.3, U7.5, U8.7
/power-supply/+12V: C10.2, P8.5, U2.10
/power-supply/-7V: C3.1, C5.1, L1.1, P8.4, R2.2
/power-supply/CAP: C9.1, C10.1, R7.2, U2.1
/power-supply/DN: C6.2, L1.2, U2.5
/power-supply/FBN: C5.2, R2.1, U2.7
/power-supply/FBP: R7.1, U2.9
/power-supply/GND: C1.2, C2.2, C3.2, C4.2, C7.2, C8.2, C9.2, C11.2, C14.2, C15.2, C16.2, C21.2, C25.2, D1.2, P8.1, R4.2, R5.2, R6.2, R9.2, R17.2, U1.5, U1.6, U1.16, U2.11, U3.3, U3.9, U3.11, U7.1, U8.4, U8.6, U8.9
/power-supply/V_BAT: C1.1, D1.1, R1.1, R3.1, U1.1, U1.2, U1.3, U1.4
unnamed: C6.1, L2.1, U2.4
unnamed: C7.1, U2.8
unnamed: C8.1, U1.9
unnamed: C16.1, R8.2, R9.1, U8.2
unnamed: C20.1, U7.6
unnamed: C20.2, L8.1, U7.2
unnamed: C48.2, U11.A4
unnamed: C49.2, U11.A7
unnamed: L3.1, U3.4
unnamed: L3.2, U3.2
unnamed: L4.2, U2.2
unnamed: R1.2, U1.15
unnamed: R3.2, U1.14
unnamed: R4.1, U1.7
unnamed: R5.1, U1.8
unnamed: R6.1, U1.13
unnamed: R8.1, U8.1
unnamed: R16.2, R17.1, U7.4
